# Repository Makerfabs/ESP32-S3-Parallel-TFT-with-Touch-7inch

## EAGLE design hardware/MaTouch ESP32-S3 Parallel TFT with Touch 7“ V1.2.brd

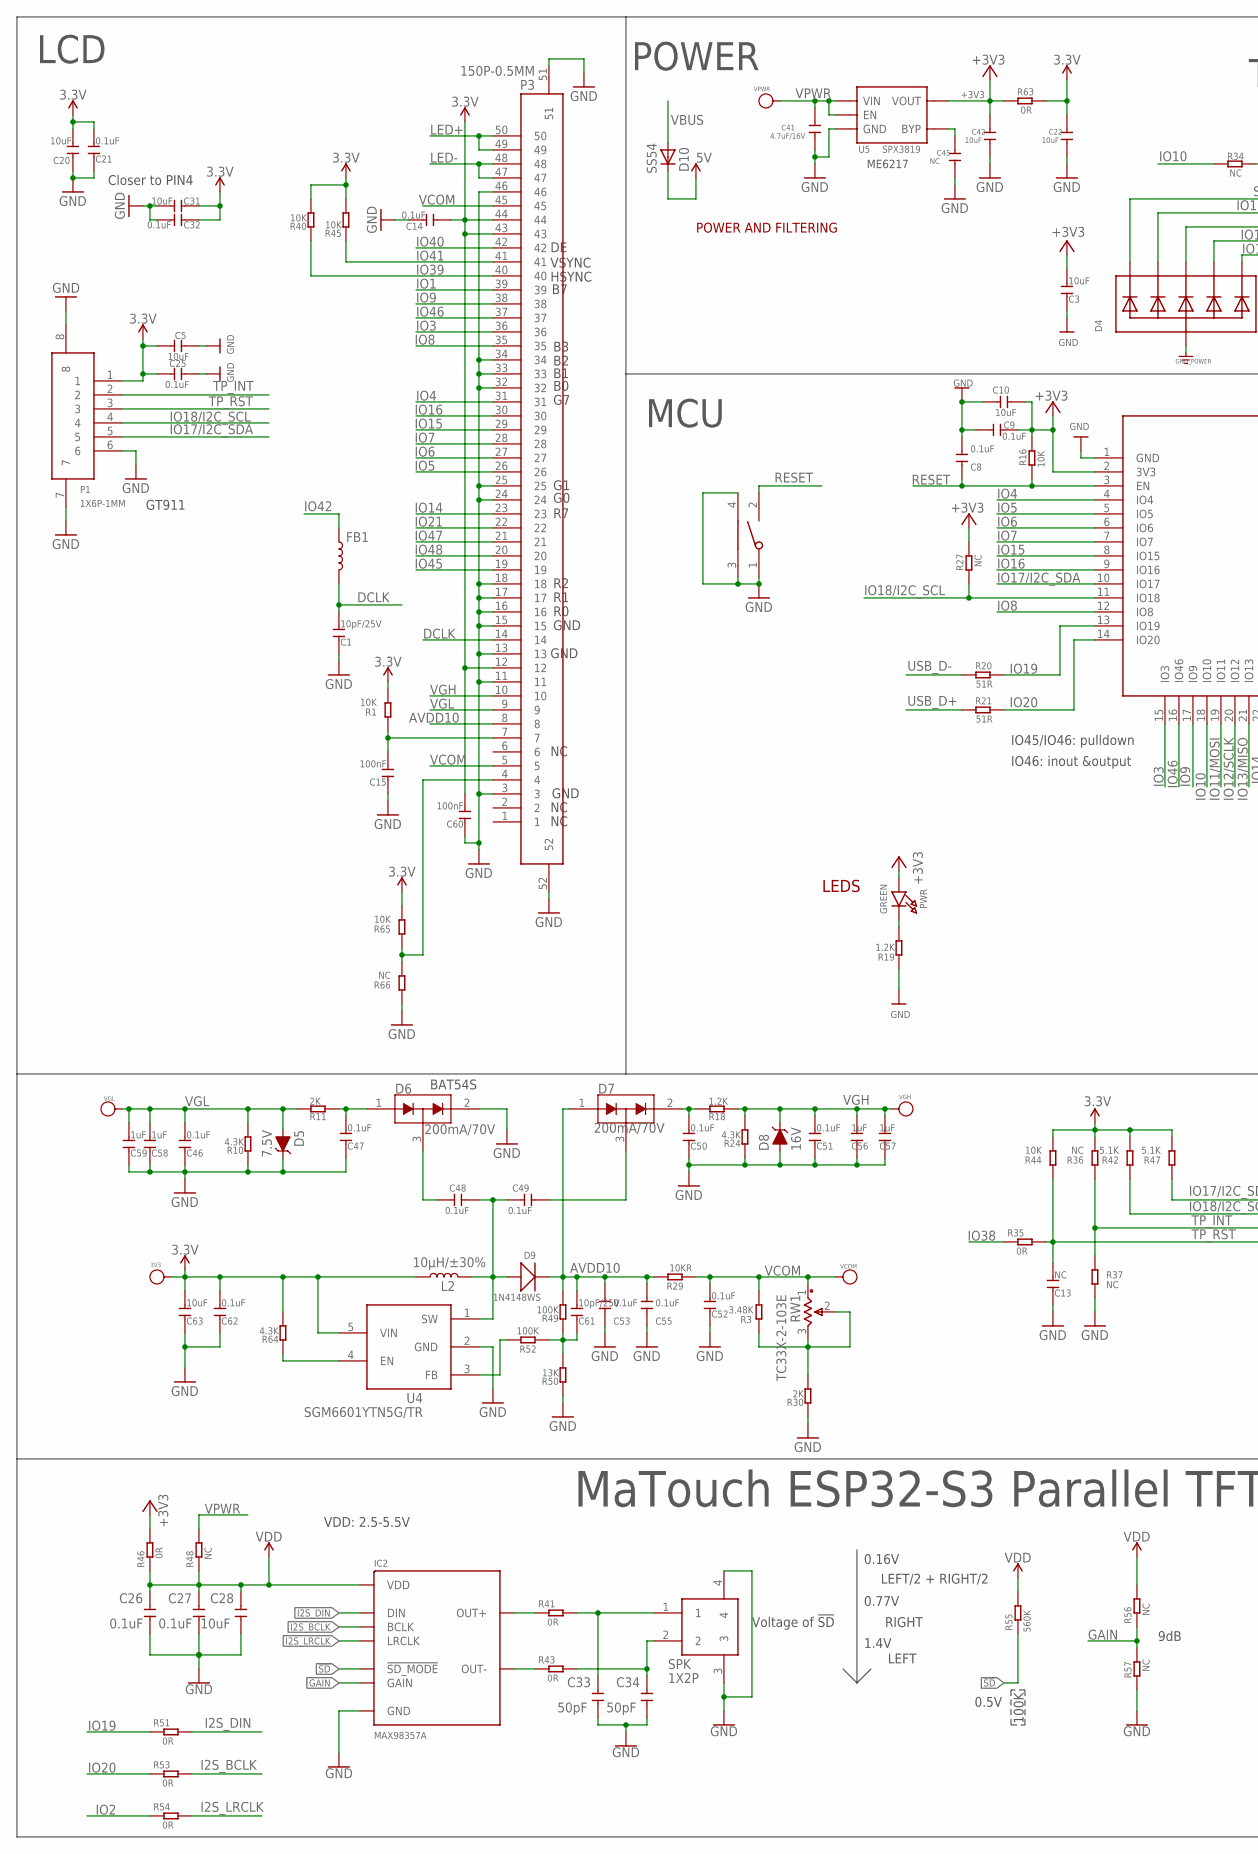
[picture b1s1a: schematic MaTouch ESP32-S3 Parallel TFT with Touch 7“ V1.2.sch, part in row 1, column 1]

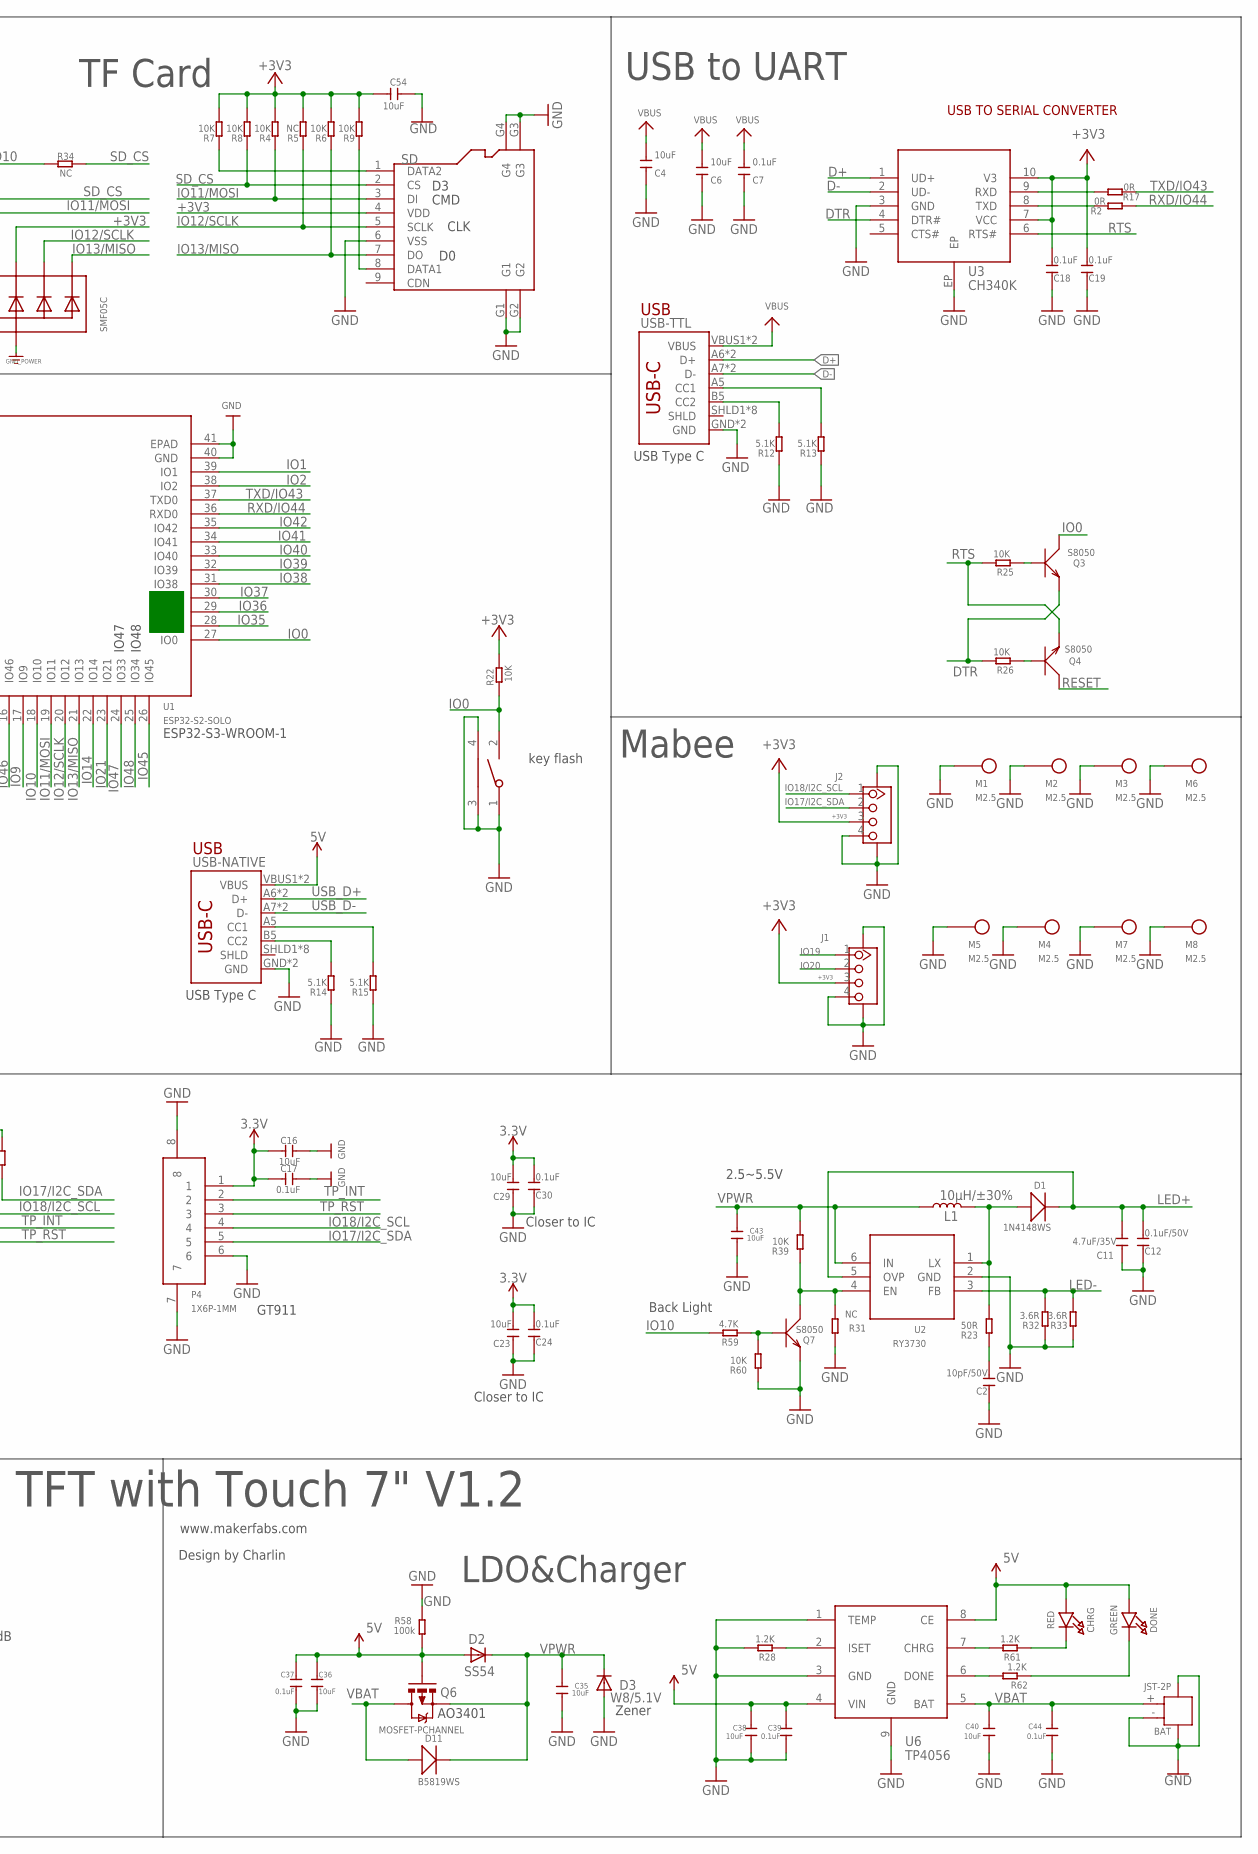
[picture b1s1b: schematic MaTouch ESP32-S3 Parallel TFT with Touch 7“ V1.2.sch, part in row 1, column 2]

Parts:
3V3: PAD-TEST-POINT-CIRCLE'4545'; TP_4545; PARTNO DNP
BAT: JST-2P; HW2-SMD-2.0-90D
BOOT: TS24CA; 2*4*3.5MM
C1, C61: 10pF/25V; DISCRETE_C0603
C2: 10pF/50V; DISCRETE_C0603
C3, C4, C5, C6, C10, C16, C20, C23, C29, C31, C54, C63: 10uF; DISCRETE_C0603
C7, C8, C9, C14, C17, C18, C19, C21, C24, C25, C30, C32, C46, C47, C48, C49, C50, C51, C52, C53, C55, C62: 0.1uF; DISCRETE_C0603
C11: 4.7uF/35V; DISCRETE_C1206
C12: 0.1uF/50V; DISCRETE_C0603
C13: NC; DISCRETE_C0603
C15, C60: 100nF; DISCRETE_C0603
C22, C28, C35, C36, C38, C40, C42, C43: 10uF; 0603
C26, C27, C37, C39, C44: 0.1uF; 0603
C33, C34: 50pF; 0603
C41: 4.7uF/16V; 0603
C45: NC; 0603
C56, C57, C58, C59: 1uF; DISCRETE_C0603
CHRG: RED; CHIPLED_0805_NOOUTLINE
D1, D9: 1N4148WS; SOD323
D2, D10: SS54; DO-214AC
D3: W8/5.1V; SOD123
D4: SMF05C; SOT363
D5: 7.5V; SOD-323
D6, D7: 200mA/70V; SOT23-3
D8: 16V; SOD-323
D11: B5819WS; SOD323
DONE: GREEN; CHIPLED_0805_NOOUTLINE
FB1: INDUCTORFB-30OHM; 0603
IC2: MAX98357A; TQFN-16
J1, J2: GROVE-CONNECTOR-SMD'90D'; HW4-SMD-2.0-90D
L1, L2: 10µH/±30%; CR54
M1, M2, M3, M4, M5, M6, M7, M8: M2.5
P1, P4: 1X6P-1MM; 1*6P-SMT1MM
P3: 150P-0.5MM; 1*50P-SMT0.5MM
PWR: GREEN; CHIPLED_0805_NOOUTLINE
Q3, Q4, Q7: S8050; SOT23
Q6: MOSFET-PCHANNEL; SOT23-3
R1, R4, R6, R7, R8, R9, R39, R40, R44, R45, R60, R65: 10K; DISCRETE_R0603
R2, R17, R35, R41, R43, R46, R51, R53, R54, R63: 0R; R0603
R3: 3.48K; DISCRETE_R0603
R5, R31, R36, R37, R66: NC; DISCRETE_R0603
R10, R24, R64: 4.3K; DISCRETE_R0603
R11, R30: 2K; DISCRETE_R0603
R12, R13, R14, R15, R42, R47: 5.1K; DISCRETE_R0603
R16, R22, R25, R26: 10K; R0603
R18, R19: 1.2K; DISCRETE_R0603
R20, R21: 51R; R0603
R23: 50R; DISCRETE_R0603
R27, R34, R48, R56, R57: NC; R0603
R28, R61, R62: 1.2K; R0603
R29: 10KR; DISCRETE_R0603
R32, R33: 3.6R; DISCRETE_R0603
R49, R52: 100K; DISCRETE_R0603
R50: 13K; DISCRETE_R0603
R55: 560K; R0603
R58: 100k; R0603
R59: 4.7K; DISCRETE_R0603
RST: TS24CA; 2*4*3.5MM
RW1: TC33X-2-103E; TC33-3MM-SMD
SD: HOLDER-MICROSD-9P; 9P-SMD-W/-RING
SPK: 1X2P; 1X2P-SMT1.25MM
U1: ESP32­S2­SOLO; ESP32-­S2-­SOLO
U2: RY3730; SOT23-6
U3: CH340K; ESOP-10-EP-150MIL
U4: SGM6601YTN5G/TR; SOT-23-5
U5: SPX3819; SOT23-5
U6: TP4056; SOP8-1.27P
USB-NATIVE: USB_C5; USB-C-16P-5
USB-TTL: USB_C5; USB-C-16P-5
VCOM: PAD-TEST-POINT-CIRCLE'4545'; TP_4545
VGH: PAD-TEST-POINT-CIRCLE'4545'; TP_4545; PARTNO DNP
VGL: PAD-TEST-POINT-CIRCLE'4545'; TP_4545; PARTNO DNP
VPWR: PAD-TEST-POINT-CIRCLE'4545'; TP_4545; PARTNO DNP

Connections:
3.3V: 3V3.T, C5.2, C14.1, C16.2, C17.2, C20.2, C21.2, C22.1, C23.2, C24.2, C25.2, C29.2, C30.2, C31.1, C32.1, C60.2, C62.2, C63.2, L2.P$1 (1), P1.1, P3.12, P3.43, P3.44, P4.1, R1.2, R36.2, R40.2, R42.2, R44.2, R45.2, R47.2, R63.2, R64.2, R65.2, U4.5 (VIN)
5V: C36.2, C37.1, C38.1, C39.1, CHRG.A, D2.A, D10.C, DONE.A, Q6.1 (G), R58.1, U6.4 (VIN), U6.8 (CE), USB-NATIVE.VBUS1 (VBUS), USB-NATIVE.VBUS2 (VBUS)
!SD: IC2.P$4 (!SD_MODE), R55.1
+3V3: C3.2, C9.1, C10.1, C18.2, C19.2, C42.1, C54.2, D4.4 (C3), J1.3, J2.3, PWR.A, R4.2, R5.2, R6.2, R7.2, R8.2, R9.2, R16.2, R22.2, R27.2, R46.2, R63.1, SD.4 (VDD), U1.2 (3V3), U3.7 (VCC), U3.10 (V3), U5.5 (VOUT)
AVDD10: C53.2, C55.2, C61.2, D7.1 (A1), D9.-, P3.8, R29.2, R49.2
D+: U3.1 (UD+), USB-TTL.A6 (D+), USB-TTL.B6 (D+)
D-: U3.2 (UD-), USB-TTL.A7 (D-), USB-TTL.B7 (D-)
DCLK: C1.2, FB1.2, P3.14
DTR: Q3.2 (E), R26.2, U3.4 (DTR#)
GAIN: IC2.P$2 (GAIN), R56.1, R57.2
GND: BAT.3, BAT.4, BAT.- (2), BOOT.1, BOOT.3, BOOT.4, C1.1, C2.1, C3.1, C4.1, C5.1, C6.1, C7.1, C8.2, C9.2, C10.2, C11.1, C12.1, C13.1, C14.2, C15.1, C16.1, C17.1, C18.1, C19.1, C20.1, C21.1, C22.2, C23.1, C24.1, C25.1, C26.1, C27.1, C28.1, C29.1, C30.1, C31.2, C32.2, C33.1, C34.1, C35.1, C36.1, C37.2, C38.2, C39.2, C40.2, C41.2, C42.2, C43.1, C44.2, C45.2, C46.1, C47.1, C50.1, C51.1, C52.1, C53.1, C54.1, C55.1, C56.1, C57.1, C58.1, C59.1, C60.1, C62.1, C63.1, D3.A, D4.2 (A), D5.C, D6.2 (C2), D8.A, IC2.P$3 (GND), IC2.P$11 (GND), IC2.P$15 (GND), IC2.P$EP (GND), J1.4, J1.SS1, J1.SS2, J2.4, J2.SS1, J2.SS2, M1.1, M2.1, M3.1, M4.1, M5.1, M6.1, M7.1, M8.1, P1.6, P1.7, P1.8, P3.3, P3.11, P3.13, P3.15, P3.16, P3.17, P3.18, P3.24, P3.25, P3.32, P3.33, P3.34, P3.46, P3.51, P3.52, P4.6, P4.7, P4.8, Q7.2 (E), R10.1, R12.1, R13.1, R14.1, R15.1, R19.1, R24.1, R28.2, R30.1, R31.1, R32.1, R33.1, R37.2, R50.1, R57.1, R58.2, R60.1, R66.1, RST.1, RST.3, RST.4, SD.6 (VSS), SD.G1, SD.G2, SD.G3, SD.G4, SPK.3, SPK.4, U1.1 (GND), U1.40 (GND), U1.41 (EPAD), U2.2 (GND), U3.3 (GND), U3.EP, U4.2 (GND), U5.2 (GND), U6.1 (TEMP), U6.3 (GND), U6.9 (GND), USB-NATIVE.GND, USB-NATIVE.GND2 (GND), USB-TTL.GND, USB-TTL.GND2 (GND)
I2S_BCLK: IC2.P$16 (BCLK), R53.2
I2S_DIN: IC2.P$1 (DIN), R51.2
I2S_LRCLK: IC2.P$14 (LRCLK), R54.2
IO0: BOOT.2, Q3.3 (C), R22.1, U1.27 (IO0)
IO1: P3.39, U1.39 (IO1)
IO2: R54.1, U1.38 (IO2)
IO3: P3.36, U1.15 (IO3)
IO4: P3.31, U1.4 (IO4)
IO5: P3.26, U1.5 (IO5)
IO6: P3.27, U1.6 (IO6)
IO7: P3.28, U1.7 (IO7)
IO8: P3.35, U1.12 (IO8)
IO9: P3.38, U1.17 (IO9)
IO10: R34.1, R59.2, U1.18 (IO10)
IO11/MOSI: D4.3 (C2), R4.1, SD.3 (DI), U1.19 (IO11)
IO12/SCLK: D4.5 (C4), R5.1, SD.5 (SCLK), U1.20 (IO12)
IO13/MISO: D4.6 (C5), R6.1, SD.7 (DO), U1.21 (IO13)
IO14: P3.23, U1.22 (IO14)
IO15: P3.29, U1.8 (IO15)
IO16: P3.30, U1.9 (IO16)
IO17/I2C_SDA: J2.2, P1.5, P4.5, R47.1, U1.10 (IO17)
IO18/I2C_SCL: J2.1, P1.4, P4.4, R27.1, R42.1, U1.11 (IO18)
IO19: J1.1, R20.2, R51.1, U1.13 (IO19)
IO20: J1.2, R21.2, R53.1, U1.14 (IO20)
IO21: P3.22, U1.23 (IO21)
IO35: U1.28 (IO35)
IO36: U1.29 (IO36)
IO37: U1.30 (IO37)
IO38: R35.1, U1.31 (IO38)
IO39: P3.40, R40.1, U1.32 (IO39)
IO40: P3.42, U1.33 (IO40)
IO41: P3.41, R45.1, U1.34 (IO41)
IO42: FB1.1, U1.35 (IO42)
IO45: P3.19, U1.26 (IO45)
IO46: P3.37, U1.16 (IO46)
IO47: P3.21, U1.24 (IO33)
IO48: P3.20, U1.25 (IO34)
LCD_RST: C15.2, P3.7, R1.1
LED+: C11.2, C12.2, D1.-, P3.49, P3.50, U2.5 (OVP)
LED-: P3.47, P3.48, R32.2, R33.2, U2.3 (FB)
unnamed: C47.2, D6.1 (A1), R11.1
unnamed: Q4.1 (B), R26.1
unnamed: Q3.1 (B), R25.1
unnamed: C61.1, R49.1, R50.2, R52.1
unnamed: P3.4, R65.1, R66.2
unnamed: R15.2, USB-NATIVE.A5 (CC1)
unnamed: PWR.C, R19.2
unnamed: C48.2, D6.3 (COM)
unnamed: C48.1, C49.2, D9.+, L2.P$2 (2), U4.1 (SW)
unnamed: R13.2, USB-TTL.A5 (CC1)
unnamed: R12.2, USB-TTL.B5 (CC2)
unnamed: C49.1, D7.3 (COM)
unnamed: C50.2, D7.2 (C2), R18.2
unnamed: R14.2, USB-NATIVE.B5 (CC2)
unnamed: R52.2, U4.3 (FB)
unnamed: R3.1, R30.2, RW1.2, RW1.3
unnamed: D1.+, L1.P$2 (2), R23.2, U2.1 (LX)
unnamed: R64.1, U4.4 (EN)
unnamed: IC2.P$9 (OUT+), R41.1
unnamed: C2.2, R23.1
unnamed: IC2.P$10 (OUT-), R43.1
unnamed: Q7.3 (C), R31.2, R39.1, U2.4 (EN)
unnamed: C33.2, R41.2, SPK.1
unnamed: C34.2, R43.2, SPK.2
unnamed: Q7.1 (B), R59.1, R60.2
unnamed: R28.1, U6.2 (ISET)
unnamed: R61.2, U6.7 (CHRG)
unnamed: R62.2, U6.6 (DONE)
unnamed: CHRG.C, R61.1
unnamed: DONE.C, R62.1
unnamed: R17.2, U3.9 (RXD)
unnamed: R7.1, SD.1 (DATA2)
unnamed: R9.1, SD.8 (DATA1)
unnamed: R2.2, U3.8 (TXD)
unnamed: C45.1, U5.4 (BYP)
RESET: C8.1, Q4.3 (C), R16.1, RST.2, U1.3 (EN)
RTS: Q4.2 (E), R25.2, U3.6 (RTS#)
RXD/IO44: R2.1, U1.36 (RXD0)
SD_CS: D4.1 (C1), R8.1, R34.2, SD.2 (CS)
TP_INT: P1.2, P4.2, R36.1, R37.1
TP_RST: C13.2, P1.3, P4.3, R35.2, R44.1
TXD/IO43: R17.1, U1.37 (TXD0)
USB_D+: R21.1, USB-NATIVE.A6 (D+), USB-NATIVE.B6 (D+)
USB_D-: R20.1, USB-NATIVE.A7 (D-), USB-NATIVE.B7 (D-)
VBAT: BAT.+ (1), C40.1, C44.1, D11.+, Q6.3 (D), U6.5 (BAT)
VBUS: C4.2, C6.2, C7.2, D10.A, USB-TTL.VBUS1 (VBUS), USB-TTL.VBUS2 (VBUS)
VCOM: C52.2, P3.5, P3.45, R3.2, R29.1, RW1.1, VCOM.T
VDD: C26.2, C27.2, C28.2, IC2.P$7 (VDD), IC2.P$8 (VDD), R46.1, R48.1, R55.2, R56.2
VGH: C51.2, C56.2, C57.2, D8.C, P3.10, R18.1, R24.2, VGH.T
VGL: C46.2, C58.2, C59.2, D5.A, P3.9, R10.2, R11.2, VGL.T
VPWR: C35.2, C41.1, C43.2, D2.C, D3.C, D11.-, L1.P$1 (1), Q6.2 (S), R39.2, R48.2, U2.6 (IN), U5.1 (VIN), U5.3 (EN), VPWR.T

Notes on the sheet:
www.makerfabs.com
Design by Charlin
USB
LEDS
POWER AND FILTERING
USB TO SERIAL CONVERTER
MaTouch ESP32-S3 Parallel TFT with Touch 7" V1.2
POWER
USB to UART
USB Type C
TF Card
GT911
Closer to IC
Back Light
IO45/IO46: pulldown
IO46: inout &output
Mabee
LCD
MCU
ESP32-S3-WROOM-1
IO47
IO48
Closer to PIN4
VDD: 2.5-5.5V
0.16V
0.77V
1.4V
LEFT/2 + RIGHT/2
RIGHT
LEFT
0.5V
100K
9dB
Voltage of !SD
LDO&Charger
AO3401
ME6217
VSYNC
HSYNC
GND

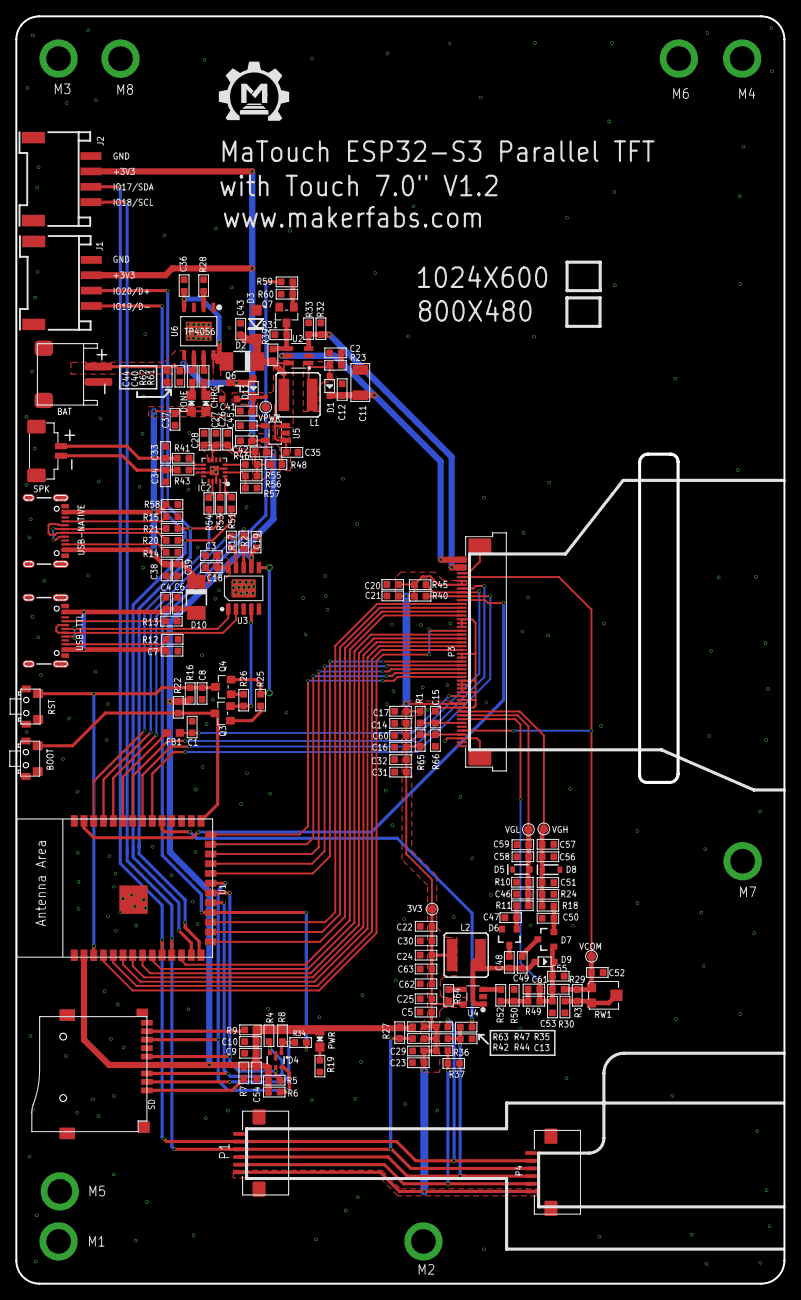
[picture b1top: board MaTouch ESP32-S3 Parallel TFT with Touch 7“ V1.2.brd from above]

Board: 2 copper layers, 100.0 x 165.0 mm, 183 parts (0 on the bottom side), 99 nets.

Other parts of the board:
U$1: MAKERFABS_0.3

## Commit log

2023-06-10 Create project
2023-06-12 Add two version screen
2023-06-12 Fix sd file
2023-06-12 Fix image
2023-06-14 Add touch demo
2023-06-14 Add lvgl fps demo
2023-06-14 Add lvgl demo
2023-08-01 Add lovyangfx demo
2023-08-05 Add schematic of PDF version
2023-10-23 Fix touch bug
2023-11-02 Add lvgl clock example
2024-09-25 Add platform demo
2025-05-22 Add Espressif ESP32_Display_Panel examples
2025-09-22 update esphome example

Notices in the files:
parts and their libraries:
microbuilder: This work is placed in the public domain, and may be freely used for commercial and non-commercial work with the following conditions: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
SparkFun-Coils: Licensing: Creative Commons ShareAlike 4.0 International - https://creativecommons.org/licenses/by-sa/4.0
